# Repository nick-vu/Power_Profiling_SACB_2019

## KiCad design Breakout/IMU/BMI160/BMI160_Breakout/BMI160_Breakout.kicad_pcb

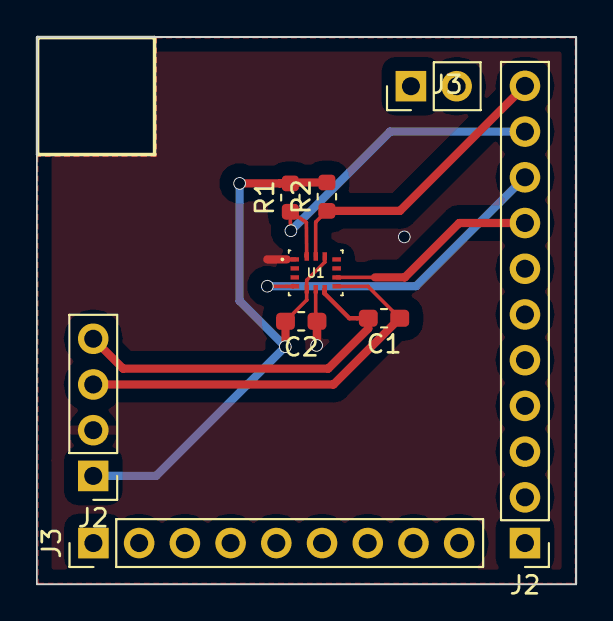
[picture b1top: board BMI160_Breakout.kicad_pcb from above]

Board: 2 copper layers, 30.0 x 30.4 mm, 9 parts (0 on the bottom side), 8 nets.

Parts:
C1, C2: 100nF; C_0603_1608Metric_Pad1.05x0.95mm_HandSolder
J2: Conn_01x04; PinHeader_1x04_P2.54mm_Vertical
J2#2: Conn_01x11; PinHeader_1x11_P2.54mm_Vertical
J3: Conn_01x02; PinHeader_1x02_P2.54mm_Vertical
J3#2: Conn_01x09; PinHeader_1x09_P2.54mm_Vertical
R1: 100K; R_0603_1608Metric
R2: 100k; R_0603_1608Metric
U1: BMI160; BMI160-Fixedtolerance

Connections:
/BMI_INT1: J2#2.9, U1.4
/BMI_INT2: J2#2.8, U1.9
/BMI_SCL: J2#2.11, R2.1, U1.13
/BMI_SDA: J2#2.10, R1.1, U1.14
AGND: C1.2, J2.4, U1.7
AVDD: C1.1, J2.3, U1.8
DGND: C2.1, J2.2, U1.1, U1.6
DVDD: C2.2, J2.1, R1.2, R2.2, U1.5, U1.12

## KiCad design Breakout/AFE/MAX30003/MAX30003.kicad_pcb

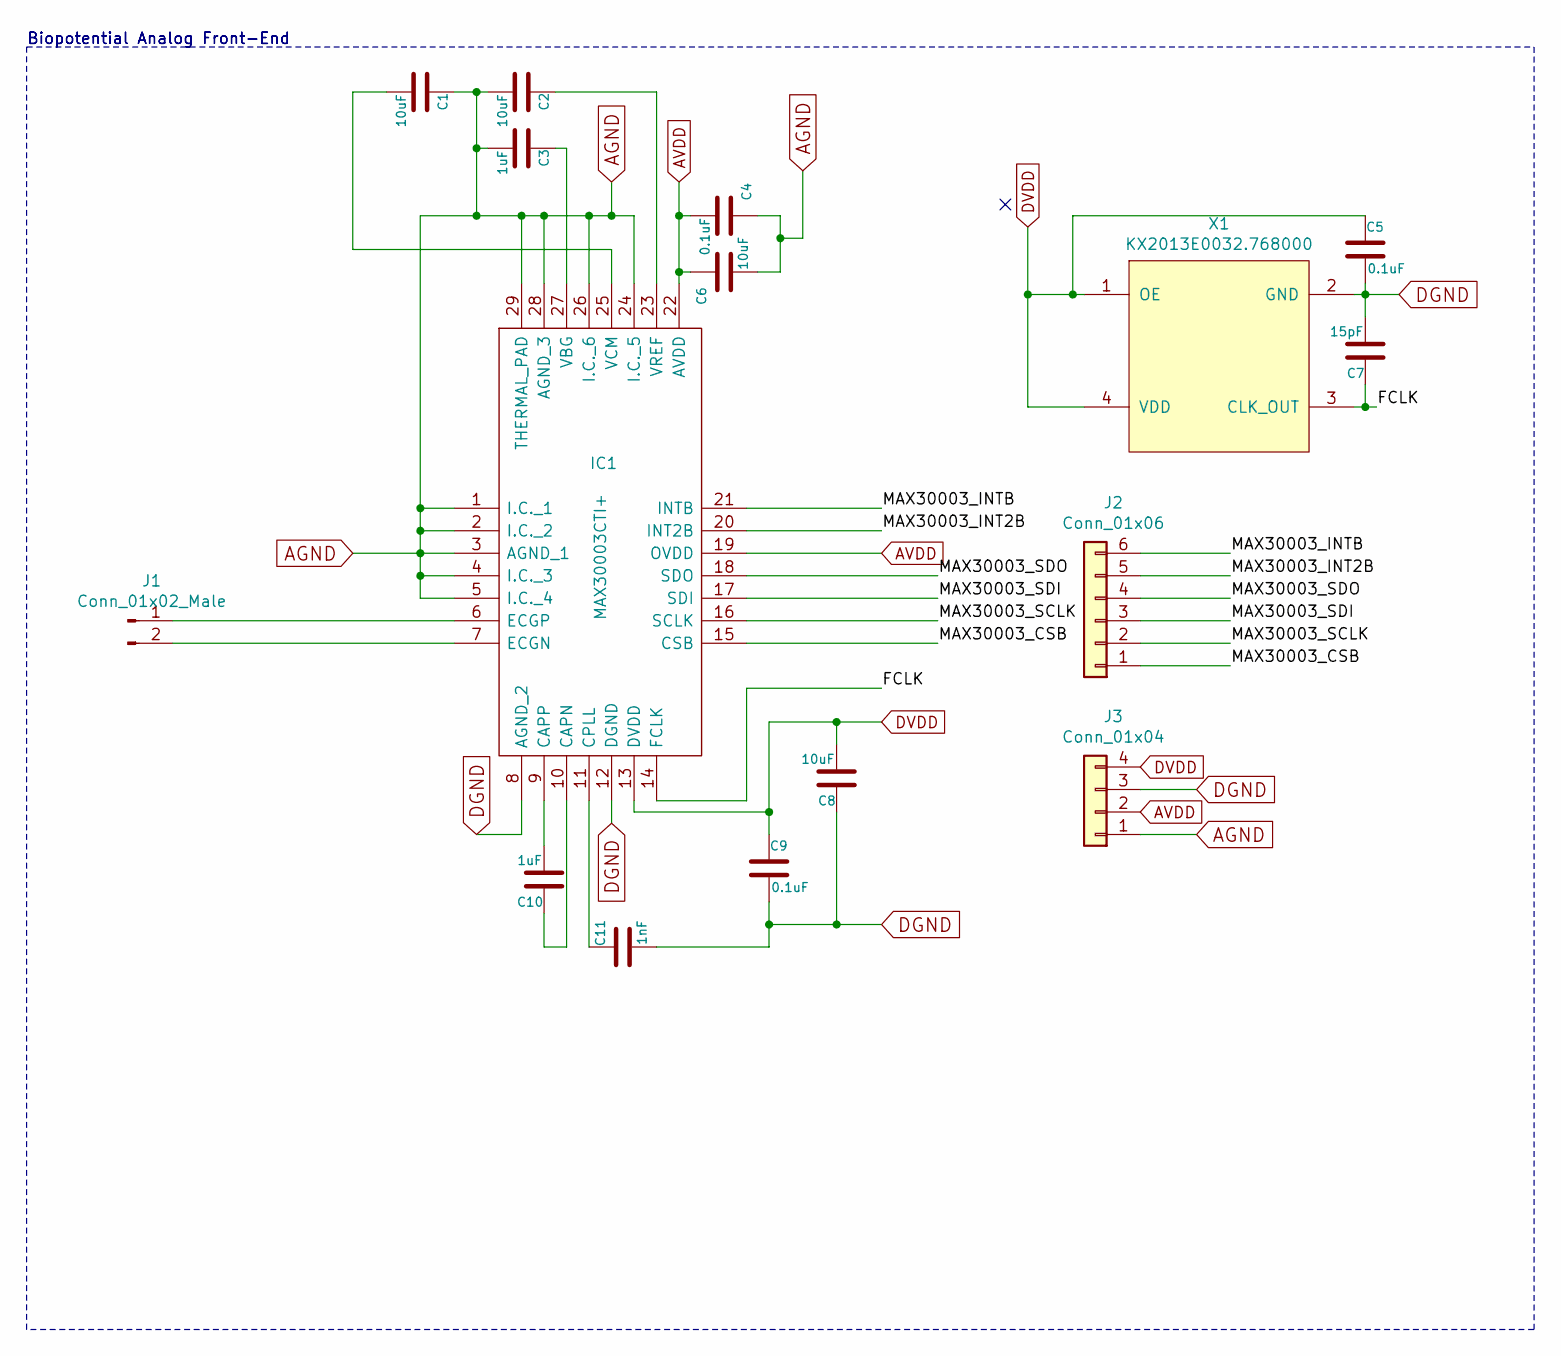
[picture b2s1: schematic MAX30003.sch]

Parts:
C1, C2, C6, C8: 10uF; C_0805_2012Metric
C3, C10: 1uF; C_0603_1608Metric
C4, C5, C9: 0.1uF; C_0603_1608Metric
C7: 15pF; C_0603_1608Metric
C11: 1nF; C_0603_1608Metric
IC1: MAX30003CTI+; QFN50P500X500X80-29N; Mouser Part Number 700-MAX30003CTI+
J1: Conn_01x02_Male; PinHeader_1x02_P2.54mm_Vertical
J2: Conn_01x06; PinHeader_1x11_P2.54mm_Vertical
J3: Conn_01x04; PinHeader_1x04_P2.54mm_Vertical
X1: KX2013E0032.768000; Crystal_SMD_2016-4Pin_2.0x1.6mm

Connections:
/FCLK: C7.1, IC1.14 (FCLK), X1.3 (CLK_OUT)
/MAX30003_CSB: IC1.15 (CSB), J2.1
/MAX30003_INT2B: IC1.20 (INT2B), J2.5
/MAX30003_INTB: IC1.21 (INTB), J2.6
/MAX30003_SCLK: IC1.16 (SCLK), J2.2
/MAX30003_SDI: IC1.17 (SDI), J2.3
/MAX30003_SDO: IC1.18 (SDO), J2.4
AGND: C1.1, C2.2, C3.2, C4.1, C6.2, IC1.1 (I.C._1), IC1.2 (I.C._2), IC1.3 (AGND_1), IC1.4 (I.C._3), IC1.5 (I.C._4), IC1.24 (I.C._5), IC1.26 (I.C._6), IC1.28 (AGND_3), IC1.29 (THERMAL_PAD), J3.1
AVDD: C4.2, C6.1, IC1.19 (OVDD), IC1.22 (AVDD), J3.2
DGND: C5.2, C7.2, C8.1, C9.2, C11.2, IC1.8 (AGND_2), IC1.12 (DGND), J3.3, X1.2 (GND)
DVDD: C5.1, C8.2, C9.1, IC1.13 (DVDD), J3.4, X1.1 (OE), X1.4 (VDD)
unnamed: C1.2, IC1.25 (VCM)
unnamed: C2.1, IC1.23 (VREF)
unnamed: C3.1, IC1.27 (VBG)
unnamed: C10.1, IC1.10 (CAPN)
unnamed: C10.2, IC1.9 (CAPP)
unnamed: C11.1, IC1.11 (CPLL)
unnamed: IC1.6 (ECGP), J1.1
unnamed: IC1.7 (ECGN), J1.2

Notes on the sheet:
Biopotential Analog Front-End

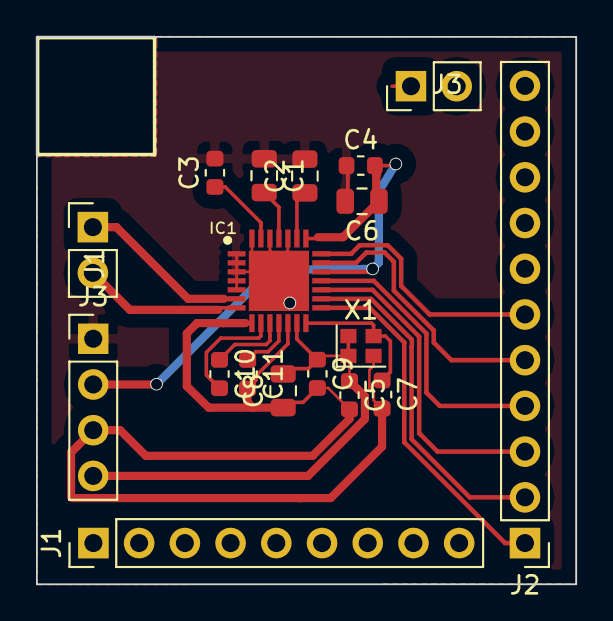
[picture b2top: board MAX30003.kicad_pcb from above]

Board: 2 copper layers, 30.0 x 30.4 mm, 18 parts (0 on the bottom side), 19 nets.

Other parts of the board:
J1#2: Conn_01x09; PinHeader_1x09_P2.54mm_Vertical
J3#2: Conn_01x02; PinHeader_1x02_P2.54mm_Vertical

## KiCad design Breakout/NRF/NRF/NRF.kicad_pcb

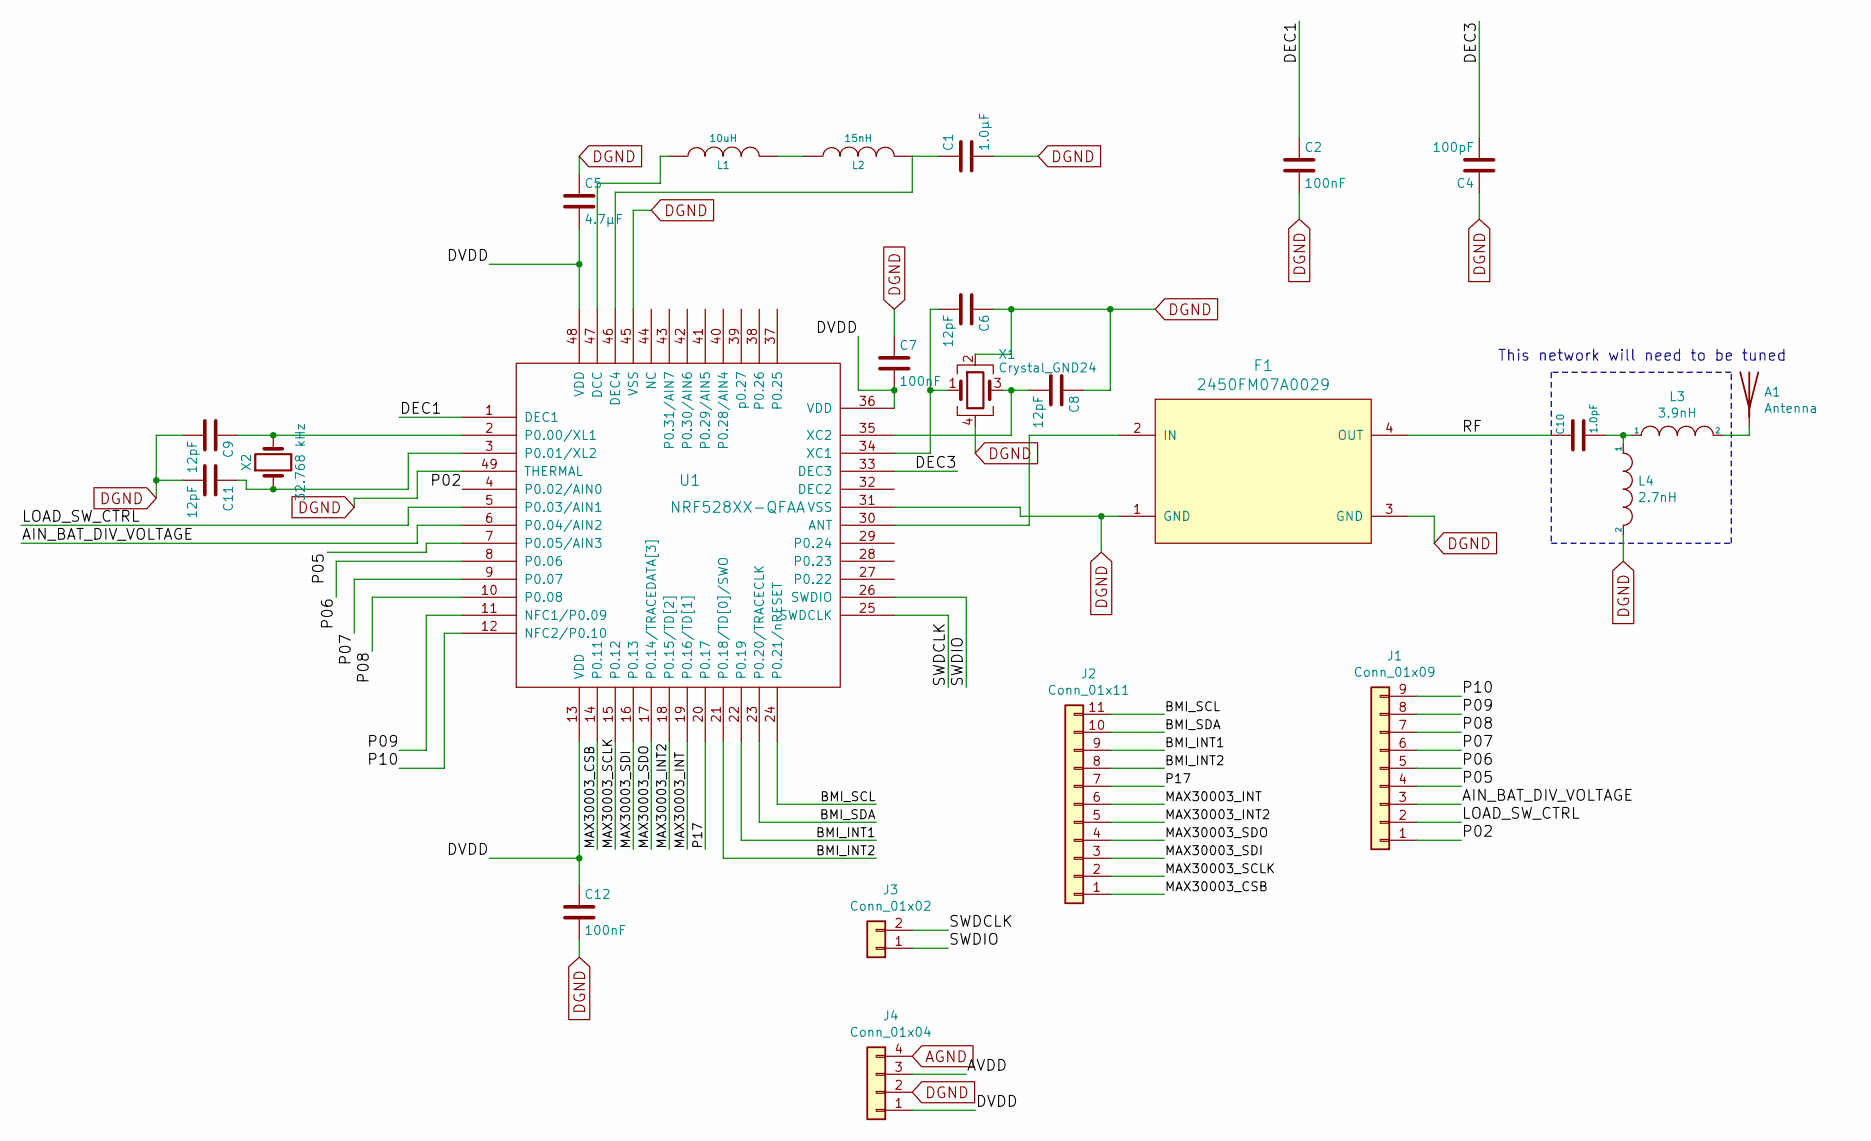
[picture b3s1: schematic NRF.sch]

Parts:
A1: Antenna; JTI-2450AT18A100-CHIP-ANT
C1: 1.0µF; C_0603_1608Metric
C2, C7, C12: 100nF; C_0402_1005Metric
C4: 100pF; C_0402_1005Metric
C5: 4.7µF; C_0402_1005Metric
C6, C8, C9, C11: 12pF; C_0402_1005Metric
C10: 1.0pF; C_0402_1005Metric
F1: 2450FM07A0029; R_0402
J1: Conn_01x09; PinHeader_1x09_P2.54mm_Vertical
J2: Conn_01x11; PinHeader_1x11_P2.54mm_Vertical
J3: Conn_01x02; PinHeader_1x02_P2.54mm_Vertical
J4: Conn_01x04; PinHeader_1x04_P2.54mm_Vertical
L1: 10uH; L_0603_1608Metric
L2: 15nH; L_0402
L3: 3.9nH; L_0402_1005Metric
L4: 2.7nH; L_0402_1005Metric
U1: NRF528XX-QFAA; UQFN-48-1EP_6x6mm_Pitch0.4mm
X1: Crystal_GND24; Crystal_SMD_2016-4pin_2.0x1.6mm
X2: 32.768 kHz; Crystal_SMD_2012-2pin_2.0x1.2mm

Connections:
/AIN_BAT_DIV_VOLTAGE: J1.3, U1.6 (P0.04/AIN2)
/AVDD: J4.3
/BMI_INT1: J2.9, U1.22 (P0.19)
/BMI_INT2: J2.8, U1.21 (P0.18/TD[0]/SWO)
/BMI_SCL: J2.11, U1.24 (P0.21/nRESET)
/BMI_SDA: J2.10, U1.23 (P0.20/TRACECLK)
/DEC1: C2.1, U1.1 (DEC1)
/DEC3: C4.2, U1.33 (DEC3)
/DVDD: C5.2, C7.2, C12.1, J4.1, U1.13 (VDD), U1.36 (VDD), U1.48 (VDD)
/LOAD_SW_CTRL: J1.2, U1.5 (P0.03/AIN1)
/MAX30003_CSB: J2.1, U1.14 (P0.11)
/MAX30003_INT: J2.6, U1.19 (P0.16/TD[1])
/MAX30003_INT2: J2.5, U1.18 (P0.15/TD[2])
/MAX30003_SCLK: J2.2, U1.15 (P0.12)
/MAX30003_SDI: J2.3, U1.16 (P0.13)
/MAX30003_SDO: J2.4, U1.17 (P0.14/TRACEDATA[3])
/P02: J1.1, U1.4 (P0.02/AIN0)
/P05: J1.4, U1.7 (P0.05/AIN3)
/P06: J1.5, U1.8 (P0.06)
/P07: J1.6, U1.9 (P0.07)
/P08: J1.7, U1.10 (P0.08)
/P09: J1.8, U1.11 (NFC1/P0.09)
/P10: J1.9, U1.12 (NFC2/P0.10)
/P17: J2.7, U1.20 (P0.17)
/RF: C10.1, F1.4 (OUT)
/SWDCLK: J3.2, U1.25 (SWDCLK)
/SWDIO: J3.1, U1.26 (SWDIO)
AGND: J4.4
DGND: C1.2, C2.2, C4.1, C5.1, C6.1, C7.1, C8.1, C9.2, C11.2, C12.2, F1.1 (GND), F1.3 (GND), J4.2, L4.2, U1.31 (VSS), U1.45 (VSS), U1.49 (THERMAL), X1.2, X1.4
unnamed: A1.1, L3.2
unnamed: C1.1, L2.2, U1.46 (DEC4)
unnamed: C6.2, U1.34 (XC1), X1.1
unnamed: C8.2, U1.35 (XC2), X1.3
unnamed: C9.1, U1.2 (P0.00/XL1), X2.2
unnamed: C10.2, L3.1, L4.1
unnamed: C11.1, U1.3 (P0.01/XL2), X2.1
unnamed: F1.2 (IN), U1.30 (ANT)
unnamed: L1.1, U1.47 (DCC)
unnamed: L1.2, L2.1

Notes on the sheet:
This network will need to be tuned

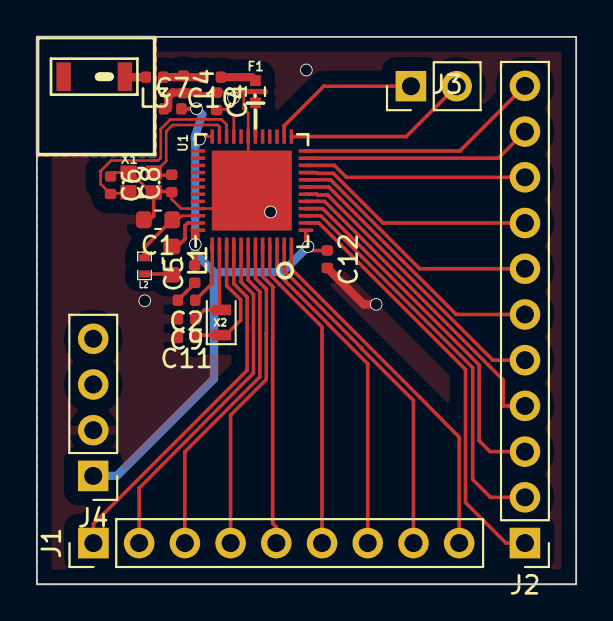
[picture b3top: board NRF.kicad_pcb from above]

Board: 2 copper layers, 30.0 x 30.4 mm, 24 parts (0 on the bottom side), 37 nets.

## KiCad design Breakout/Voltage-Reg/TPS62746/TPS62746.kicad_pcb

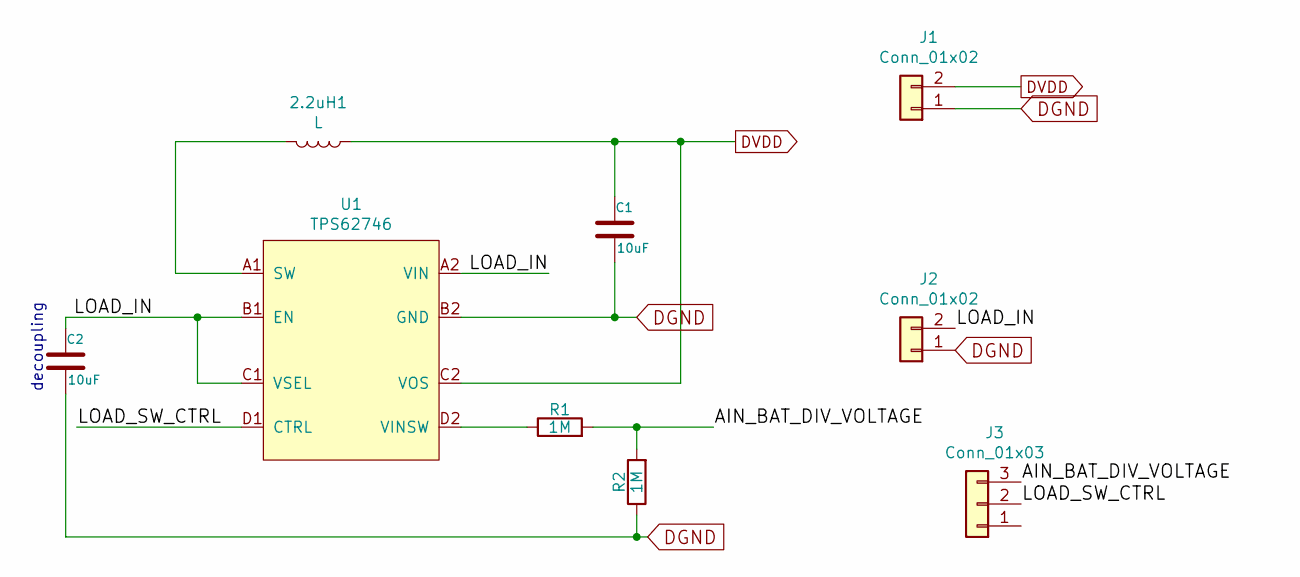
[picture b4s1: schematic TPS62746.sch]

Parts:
2.2uH1: L; L_0603_1608Metric
C1, C2: 10uF; C_0603_1608Metric
J1, J2: Conn_01x02; PinSocket_1x02_P2.54mm_Vertical
J3: Conn_01x03
R1, R2: 1M; R_0603_1608Metric
U1: TPS62746; Texas_DSBGA-8_0.9x1.9mm_Layout2x4_P0.5mm

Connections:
/AIN_BAT_DIV_VOLTAGE: J3.3, R1.2, R2.2
/LOAD_IN: C2.1, J2.2, U1.A2 (VIN), U1.B1 (EN), U1.C1 (VSEL)
/LOAD_SW_CTRL: J3.2, U1.D1 (CTRL)
DGND: C1.2, C2.2, J1.1, J2.1, R2.1, U1.B2 (GND)
DVDD: 2.2uH1.1, C1.1, J1.2, U1.C2 (VOS)
unnamed: 2.2uH1.2, U1.A1 (SW)
unnamed: R1.1, U1.D2 (VINSW)

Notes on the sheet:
decoupling

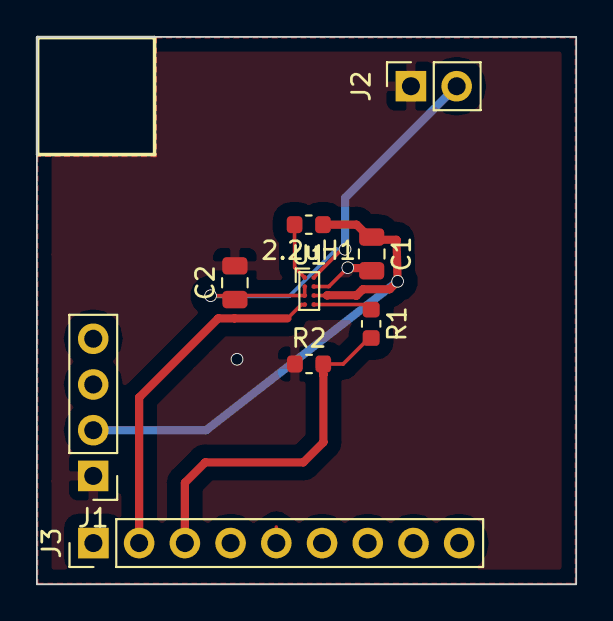
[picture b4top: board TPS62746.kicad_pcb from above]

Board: 2 copper layers, 30.0 x 30.4 mm, 9 parts (0 on the bottom side), 7 nets.

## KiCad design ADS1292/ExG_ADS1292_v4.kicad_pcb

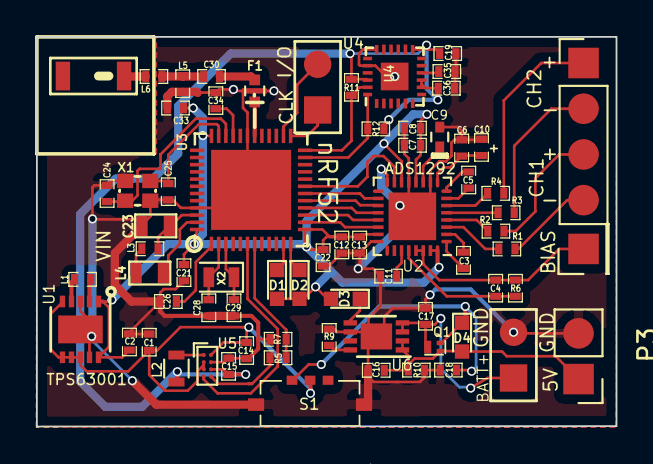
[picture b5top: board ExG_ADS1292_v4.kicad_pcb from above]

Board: 2 copper layers, 32.2 x 21.7 mm, 70 parts (0 on the bottom side), 58 nets.

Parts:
A1: CHIP-ANT; JTI-2450AT18A100-CHIP-ANT
C1, C10, C14, C15: 10uF; SM0402
C2: 22uF; SM0402
C3, C5: 4.7 nF; SM0402
C4: 1.0nF-1.5nF; SM0402
C6, C7, C12: 0.1uF; SM0402
C8, C11, C13: 1uF; SM0402
C9: 1uF; C_0402
C16, C17: 4.7uF; SM0402
C18: 1.0uF; SM0402
C19, C22, C26, C33, C35, C36: 100nF; SM0402
C21: 4.7µF; SM0402
C23: 1.0µF; SM0603
C24, C25, C28, C29: 12pF; SM0402
C30: 1.0pF; SM0402
C34: 100pF; SM0402
D1, D2, D3: LED; LED_0603
D4: D_Schottky; LED_0603
F1: 2450FM07A0029; R_0402
L1: 2.20µH; SM0402
L2: 2.2 uH; R_0603
L3: 15nH; SM0402
L4: 10uH; SM0603
L5: 2.7nH; SM0402
L6: 3.9nH; SM0402
P1, P2: CONN_2; PIN_ARRAY_2X1
P3: CONN_2; Pin_Header_Straight_1x02_Pitch2.54mm
P4: CONN_1; Pin_Header_Straight_1x01_Pitch2.54mm
P5: CONN_01X04; Pin_Header_Straight_1x04_Pitch2.54mm
Q1: DMP21D5UFB4-7B; X2-DFN1006
R1, R2, R3, R4: 30k; SM0402
R5, R7: 1M; SM0402
R6: 1MΩ; SM0402
R9: 2k; SM0402
R10: 100k; SM0402
R11, R12: 10k; SM0402
S1: SSAJ120100
U1: TPS63001; DFN-10-1EP_3x3mm_Pitch0.5mm
U2: ADS1291/2; QFN-32-1EP_4x4mm_Pitch0.4mm
U3: NRF528XX-QFAA; UQFN-48-1EP_6x6mm_Pitch0.4mm
U4: ICM-20948; QFN-24_3x3mm_Pitch0.4mm
U5: TPS62746; Texas_DSBGA-8_0.9x1.9mm_Layout2x4_P0.5mm
U6: MCP73831; DFN-8-1EP_3x2mm_Pitch0.5mm
X1: Crystal_GND24; CRYSTAL-SMD-2.0MMx1.6MM
X2: 32.768 kHz; Crystal_SMD_2012-2pin_2.0x1.2mm

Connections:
1.8V: C15.1, C19.1, C36.1, L2.2, R11.1, R12.1, U4.8, U4.9, U4.13, U4.22, U5.C2
5V_in_charge: C16.1, D4.2, P3.1, Q1.1, R10.1, U6.1, U6.2
/AIN_BAT_DIV_VOLTAGE: R5.2, R7.2, U3.7
/BATT_IN: C17.1, P1.1, Q1.2, U6.3, U6.4
/BIASIN: C4.2, P4.1, R6.2, U2.29, U2.30
/DEC1: C26.1, U3.1
/DEC3: C34.1, U3.33
/DIN: U2.19, U3.17
/DOUT: U2.21, U3.15
/IN1: P5.3, R2.2
/IN1-: P5.4, R1.2
/IN2: P5.1, R4.2
/IN2-: P5.2, R3.2
/LED2: D1.1, U3.11
/LED3: D2.1, U3.12
/LOAD_SW_CTRL: U3.6, U5.D1
/RF: C30.1, F1.4
/SCL: R11.2, U3.24, U4.23
/SDI: R12.2, U3.23, U4.24
/SPI_SCLK: U2.20, U3.16
/SPI_~CS: U2.18, U3.18
/SWDCLK: P2.1, U3.25
/SWDIO: P2.2, U3.26
/~DRDY: U2.22, U3.14
/~PWDN/RESET: U2.15, U3.19
DGND: C1.2, C2.2, C6.1, C7.1, C8.1, C9.2, C10.1, C11.2, C12.2, C13.2, C14.2, C15.2, C16.2, C17.2, C18.1, C19.2, C21.1, C22.2, C23.2, C24.1, C25.1, C26.2, C28.2, C29.2, C33.1, C34.2, C35.2, C36.2, F1.1, F1.3, L5.2, P1.2, P3.2, R7.1, R9.2, R10.2, S1.4, S1.5, U1.3, U1.9, U1.11, U2.10, U2.13, U2.16, U2.24, U2.33, U3.31, U3.45, U3.49, U4.18, U4.20, U4.25, U5.B2, U6.6, U6.9, X1.2, X1.4
DVDD: C2.1, C7.2, C8.2, C12.1, C13.1, C21.2, C22.1, C33.2, D1.2, D2.2, D3.2, U1.1, U1.10, U2.12, U2.14, U2.23, U2.31, U2.32, U3.13, U3.36, U3.48
unnamed: A1.1, L6.2
unnamed: C3.1, U2.1
unnamed: C3.2, U2.2
unnamed: C4.1, R6.1, U2.28
unnamed: C5.1, U2.7
unnamed: C5.2, U2.8
unnamed: C9.1, U2.11
unnamed: C6.2, C10.2, U2.9
unnamed: C11.1, U2.27
unnamed: C23.1, L3.2, U3.46
unnamed: C24.2, U3.34, X1.1
unnamed: C25.2, U3.35, X1.3
unnamed: C28.1, U3.2, X2.2
unnamed: C29.1, U3.3, X2.1
unnamed: C30.2, L5.1, L6.1
unnamed: C35.1, U4.10
unnamed: D3.1, U6.5
unnamed: F1.2, U3.30
unnamed: L1.1, U1.4
unnamed: L1.2, U1.2
unnamed: L2.1, U5.A1
unnamed: L3.1, L4.2
unnamed: L4.1, U3.47
unnamed: R1.1, U2.3
unnamed: R2.1, U2.4
unnamed: R3.1, U2.5
unnamed: R4.1, U2.6
unnamed: R5.1, U5.D2
unnamed: R9.1, U6.8
VCC: C1.1, C14.1, S1.3, U1.5, U1.6, U1.7, U1.8, U5.A2, U5.B1, U5.C1
VccSwitch: C18.2, D4.1, Q1.3, S1.1

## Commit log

2019-09-12 first
2019-10-11 qdone
